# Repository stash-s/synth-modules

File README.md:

# synth-modules

Analog Synth Modules schematics shamelessly copied from Internets.

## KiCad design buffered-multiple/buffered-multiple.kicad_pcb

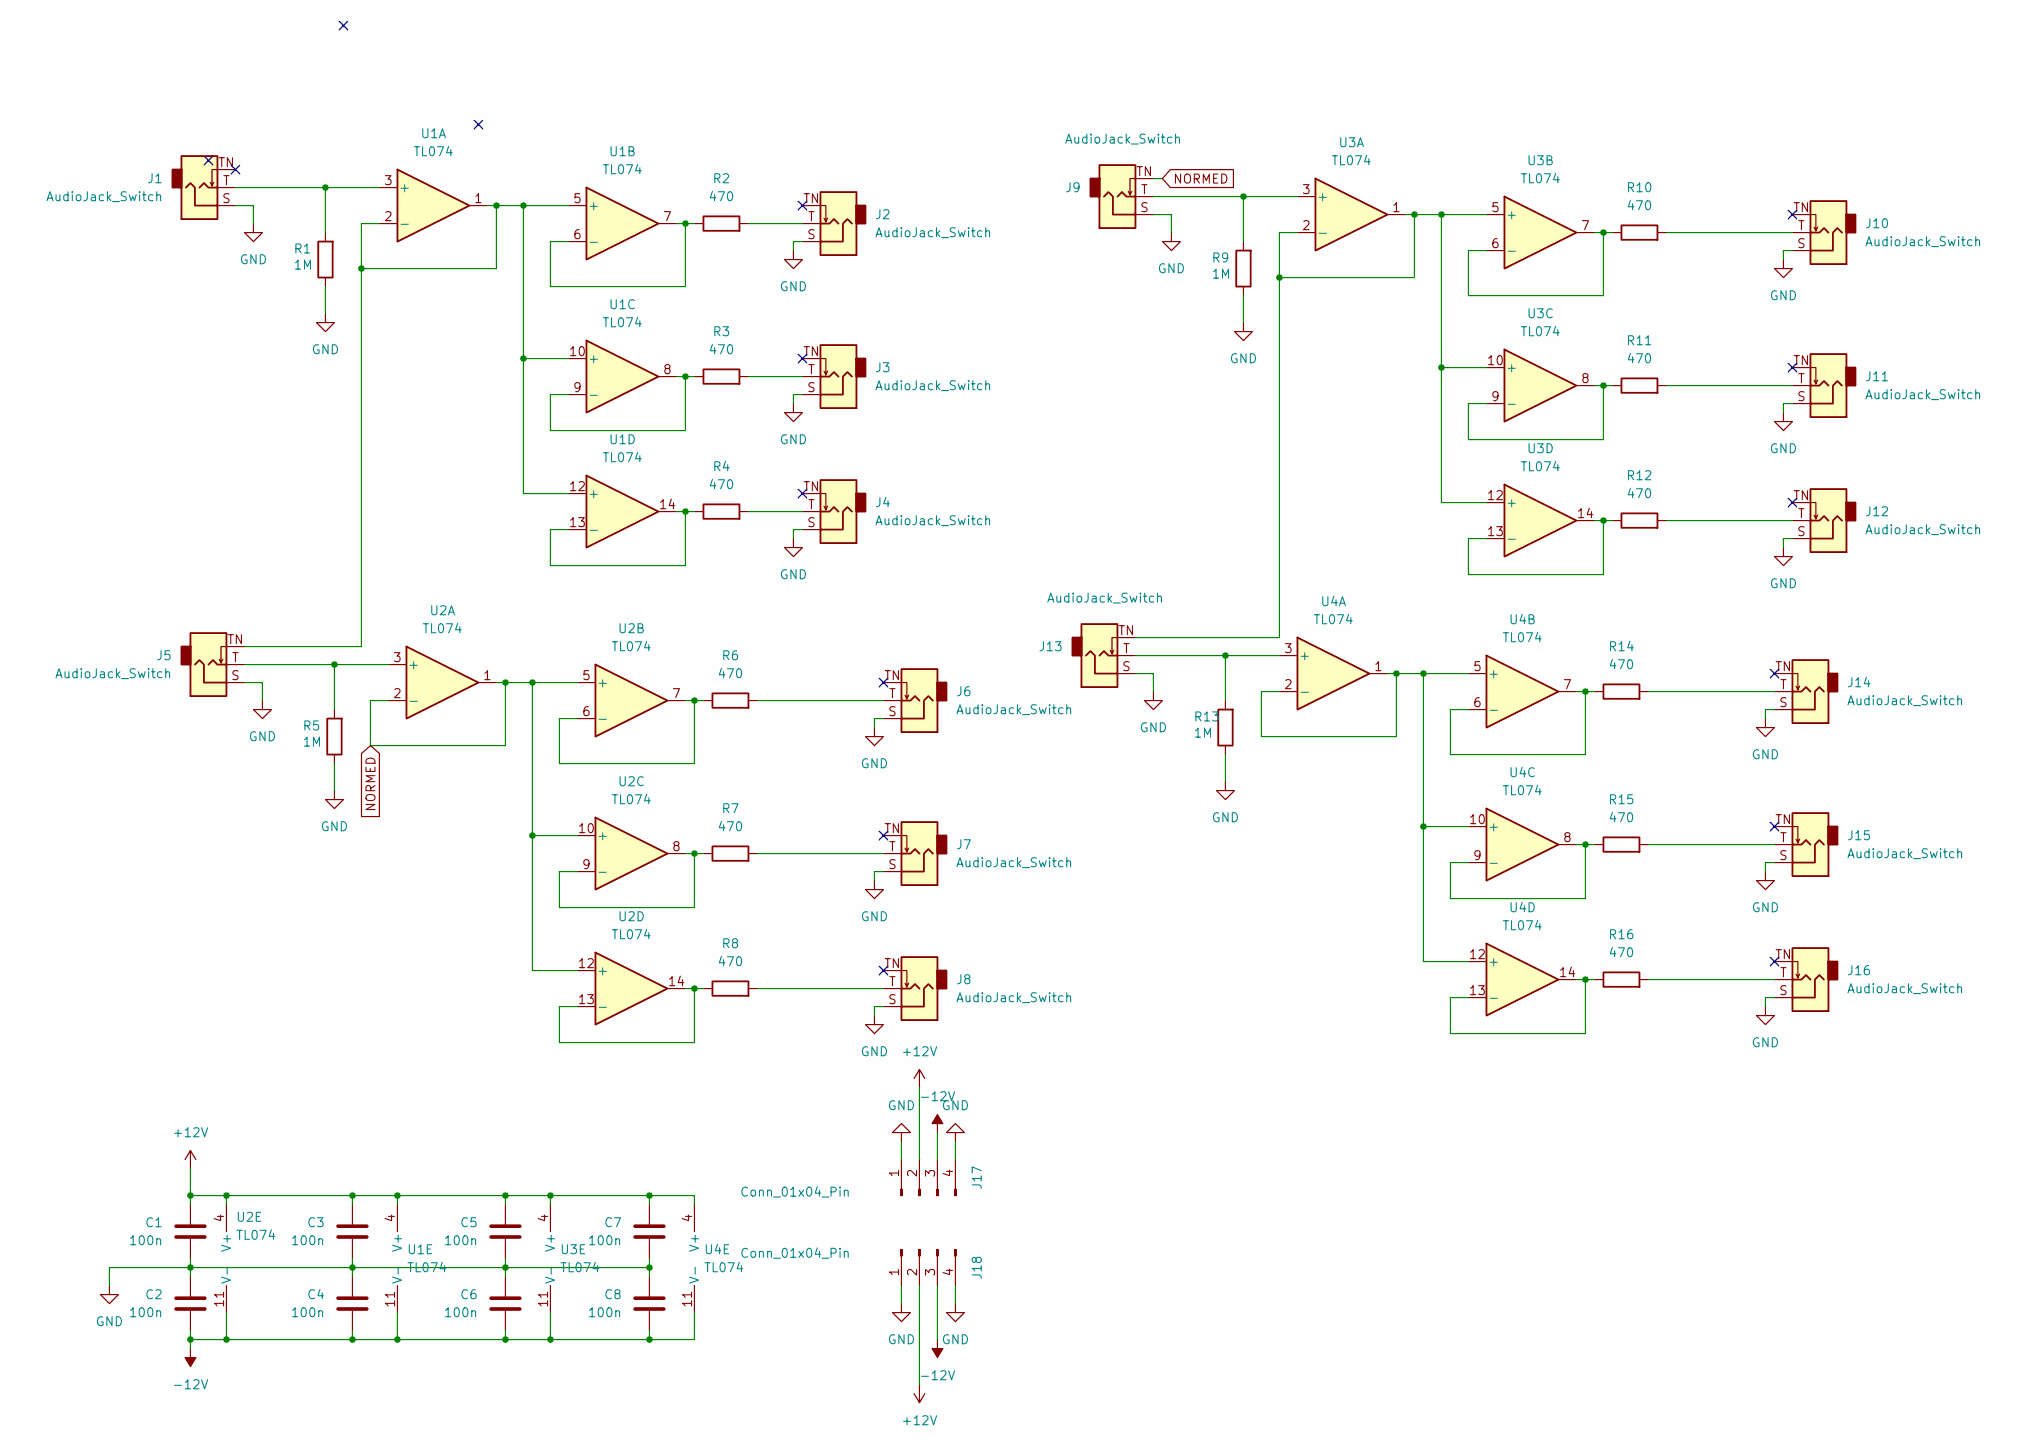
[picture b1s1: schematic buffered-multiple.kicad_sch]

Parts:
C1, C2, C3, C4, C5, C6, C7, C8: 100n; C_0402_1005Metric
J1, J2, J3, J4, J5, J6, J7, J8, J9, J10, J11, J12, J13, J14, J15, J16: AudioJack_Switch; Jack_3.5mm_Switch
J17, J18: Conn_01x04_Pin; PinHeader_1x04_P2.54mm_Vertical
R1, R5, R9, R13: 1M; R_0402_1005Metric
R2, R3, R4, R6, R7, R8, R10, R11, R12, R14, R15, R16: 470; R_0402_1005Metric
U1, U2, U3, U4: TL074; SOT-23-THIN-14_2x4.2mm_P0.5mm

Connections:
+12V: C1.1, C3.1, C5.1, C7.1, J17.2, J18.2, U1.4 (V+), U2.4 (V+), U3.4 (V+), U4.4 (V+)
-12V: C2.2, C4.2, C6.2, C8.2, J17.3, J18.3, U1.11 (V-), U2.11 (V-), U3.11 (V-), U4.11 (V-)
GND: C1.2, C2.1, C3.2, C4.1, C5.2, C6.1, C7.2, C8.1, J1.S, J2.S, J3.S, J4.S, J5.S, J6.S, J7.S, J8.S, J9.S, J10.S, J11.S, J12.S, J13.S, J14.S, J15.S, J16.S, J17.1, J17.4, J18.1, J18.4, R1.1, R5.1, R9.1, R13.1
NORMED: J9.TN, U2.1, U2.2 (-), U2.5 (+), U2.10 (+), U2.12 (+)
unnamed: J2.T, R2.2
unnamed: J3.T, R3.2
unnamed: J4.T, R4.2
unnamed: J6.T, R6.2
unnamed: J7.T, R7.2
unnamed: J8.T, R8.2
unnamed: J10.T, R10.2
unnamed: J11.T, R11.2
unnamed: J12.T, R12.2
unnamed: J14.T, R14.2
unnamed: J15.T, R15.2
unnamed: J16.T, R16.2
unnamed: J1.T, R1.2, U1.3 (+)
unnamed: J5.TN, U1.1, U1.2 (-), U1.5 (+), U1.10 (+), U1.12 (+)
unnamed: R2.1, U1.6 (-), U1.7
unnamed: R3.1, U1.8, U1.9 (-)
unnamed: R4.1, U1.13 (-), U1.14
unnamed: J5.T, R5.2, U2.3 (+)
unnamed: R6.1, U2.6 (-), U2.7
unnamed: R7.1, U2.8, U2.9 (-)
unnamed: R8.1, U2.13 (-), U2.14
unnamed: J9.T, R9.2, U3.3 (+)
unnamed: J13.TN, U3.1, U3.2 (-), U3.5 (+), U3.10 (+), U3.12 (+)
unnamed: R10.1, U3.6 (-), U3.7
unnamed: R11.1, U3.8, U3.9 (-)
unnamed: R12.1, U3.13 (-), U3.14
unnamed: J13.T, R13.2, U4.3 (+)
unnamed: U4.1, U4.2 (-), U4.5 (+), U4.10 (+), U4.12 (+)
unnamed: R14.1, U4.6 (-), U4.7
unnamed: R15.1, U4.8, U4.9 (-)
unnamed: R16.1, U4.13 (-), U4.14

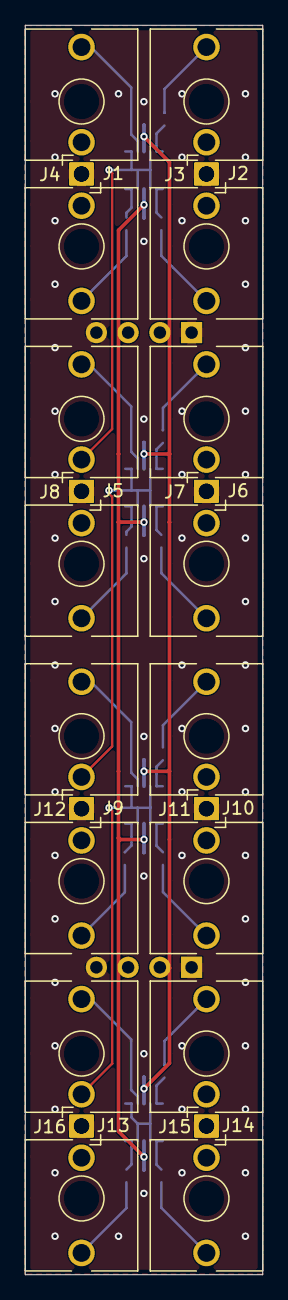
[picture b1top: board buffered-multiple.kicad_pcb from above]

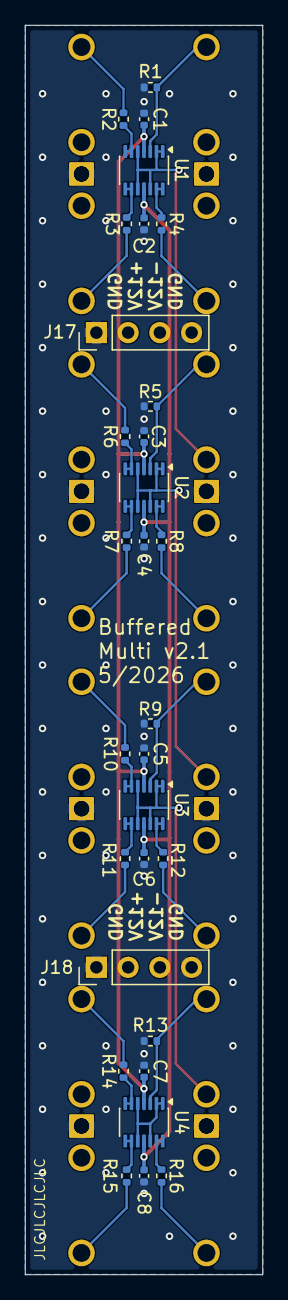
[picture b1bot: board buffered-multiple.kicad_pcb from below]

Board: 2 copper layers, 19.0 x 100.0 mm, 46 parts (30 on the bottom side), 35 nets.

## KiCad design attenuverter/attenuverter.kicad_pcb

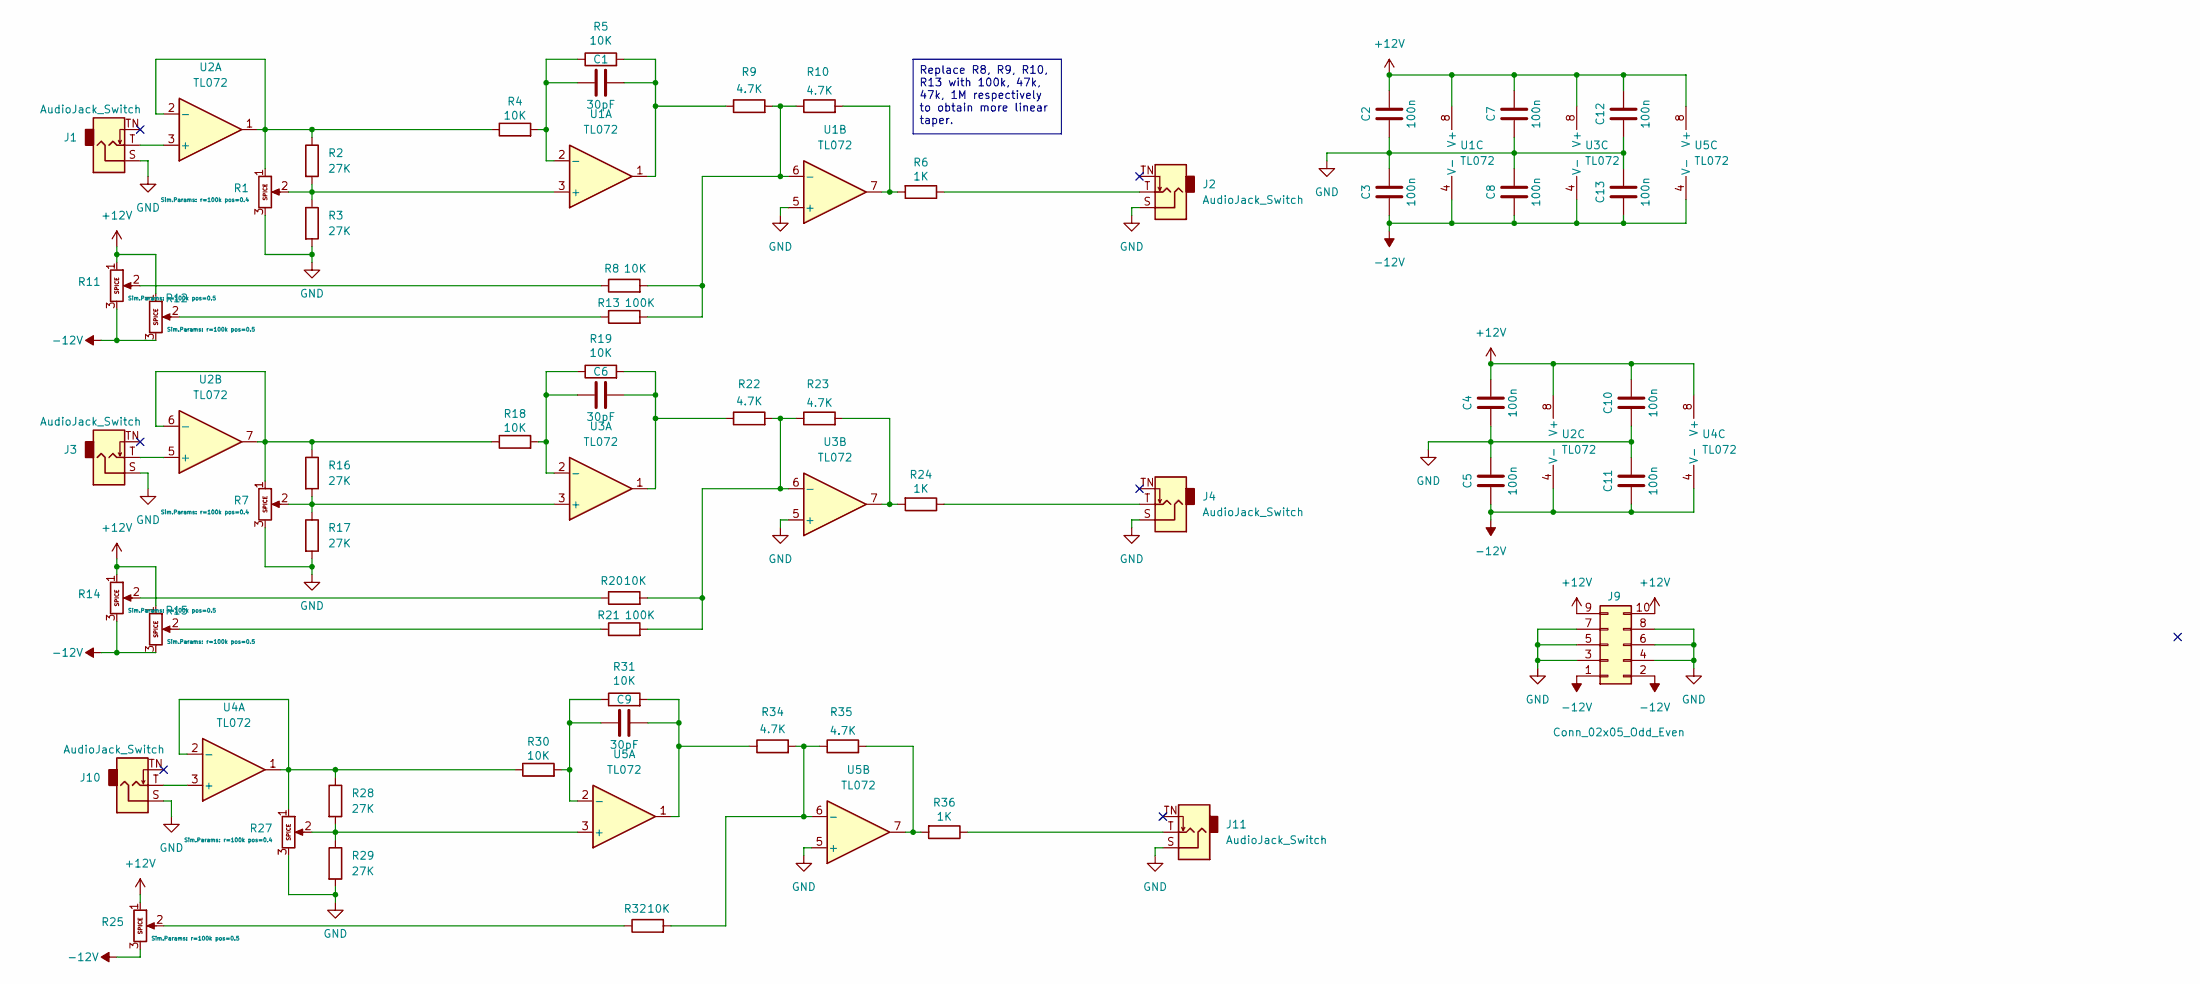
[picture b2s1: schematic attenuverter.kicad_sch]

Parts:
C1, C6, C9: 30pF; C_0402_1005Metric
C2, C3, C4, C5, C7, C8, C10, C11, C12, C13: 100n; C_0402_1005Metric
J1, J2, J3, J4, J10, J11: AudioJack_Switch; Jack_3.5mm_Switch
J9: Conn_02x05_Odd_Even; IDC-Header_2x05_P2.54mm_Vertical
R1, R7, R11, R12, R14, R15, R25, R27: 100K; Potentiometer_Alpha_RD901F-40-00D_Single_Vertical
R2, R3, R16, R17, R28, R29: 27K; R_0402_1005Metric
R4, R5, R18, R19, R30, R31: 10K; R_0402_1005Metric
R6, R24, R36: 1K; R_0402_1005Metric
R8, R20, R32: 10K; R_Axial_DIN0204_L3.6mm_D1.6mm_P5.08mm_Horizontal
R9, R10, R22, R23, R34, R35: 4.7K; R_Axial_DIN0204_L3.6mm_D1.6mm_P5.08mm_Horizontal
R13, R21: 100K; R_Axial_DIN0204_L3.6mm_D1.6mm_P5.08mm_Horizontal
U1, U2, U3, U4, U5: TL072; SOT-23-8

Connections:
+12V: C2.2, C4.2, C7.2, C10.2, C12.2, J9.9, J9.10, R11.1, R12.1, R14.1, R15.1, R25.1, U1.8 (V+), U2.8 (V+), U3.8 (V+), U4.8 (V+), U5.8 (V+)
-12V: C3.1, C5.1, C8.1, C11.1, C13.1, J9.1, J9.2, R11.3, R12.3, R14.3, R15.3, R25.3, U1.4 (V-), U2.4 (V-), U3.4 (V-), U4.4 (V-), U5.4 (V-)
GND: C2.1, C3.2, C4.1, C5.2, C7.1, C8.2, C10.1, C11.2, C12.1, C13.2, J1.S, J2.S, J3.S, J4.S, J9.3, J9.4, J9.5, J9.6, J9.7, J9.8, J10.S, J11.S, R1.3, R3.2, R7.3, R17.2, R27.3, R29.2, U1.5 (+), U3.5 (+), U5.5 (+)
unnamed: C1.1, R5.2, R9.1, U1.1
unnamed: C6.2, R19.2, R22.1, U3.1
unnamed: C9.2, R31.2, R34.1, U5.1
unnamed: J2.T, R6.1
unnamed: J4.T, R24.1
unnamed: J11.T, R36.1
unnamed: R6.2, R10.2, U1.7
unnamed: R8.1, R11.2
unnamed: R12.2, R13.1
unnamed: R14.2, R20.1
unnamed: R15.2, R21.1
unnamed: R23.2, R24.2, U3.7
unnamed: R25.2, R32.1
unnamed: R35.2, R36.2, U5.7
unnamed: R1.2, R2.2, R3.1, U1.3 (+)
unnamed: C1.2, R4.2, R5.1, U1.2 (-)
unnamed: R8.2, R9.2, R10.1, R13.2, U1.6 (-)
unnamed: J1.T, U2.3 (+)
unnamed: R1.1, R2.1, R4.1, U2.1, U2.2 (-)
unnamed: J3.T, U2.5 (+)
unnamed: R7.1, R16.1, R18.1, U2.6 (-), U2.7
unnamed: R7.2, R16.2, R17.1, U3.3 (+)
unnamed: C6.1, R18.2, R19.1, U3.2 (-)
unnamed: R20.2, R21.2, R22.2, R23.1, U3.6 (-)
unnamed: J10.T, U4.3 (+)
unnamed: R27.1, R28.1, R30.1, U4.1, U4.2 (-)
unnamed: R27.2, R28.2, R29.1, U5.3 (+)
unnamed: C9.1, R30.2, R31.1, U5.2 (-)
unnamed: R32.2, R34.2, R35.1, U5.6 (-)

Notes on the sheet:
Replace R8, R9, R10, R13 with 100k, 47k, 47k, 1M respectively to obtain more linear taper.

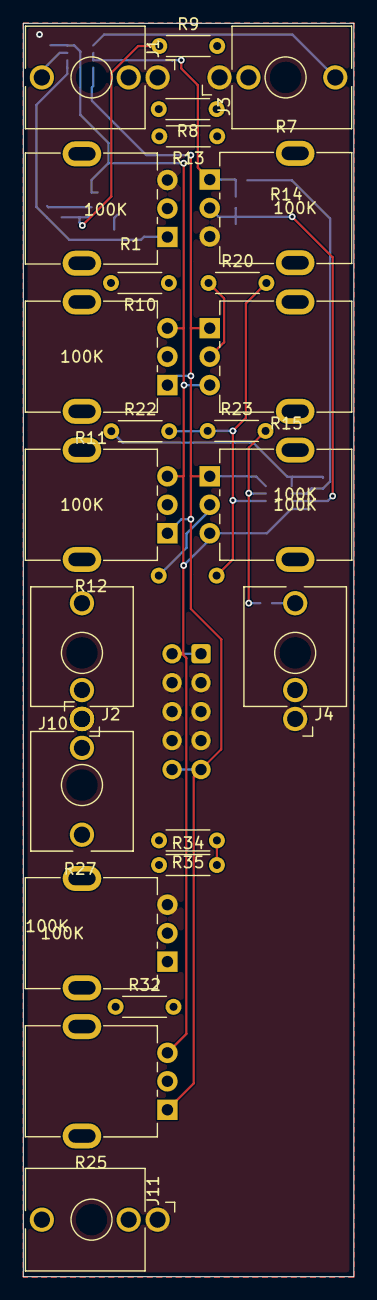
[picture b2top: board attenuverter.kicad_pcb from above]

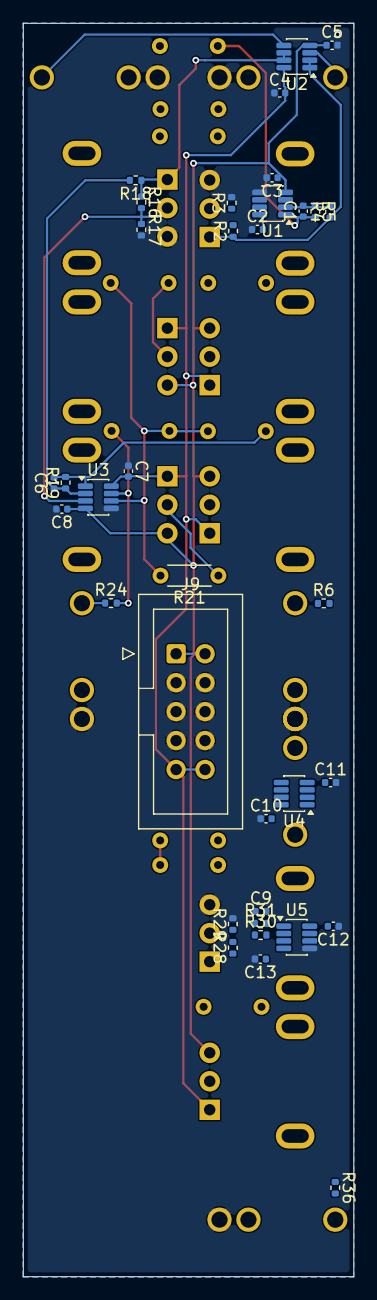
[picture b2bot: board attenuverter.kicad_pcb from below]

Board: 2 copper layers, 29.0 x 110.0 mm, 59 parts (35 on the bottom side), 32 nets.

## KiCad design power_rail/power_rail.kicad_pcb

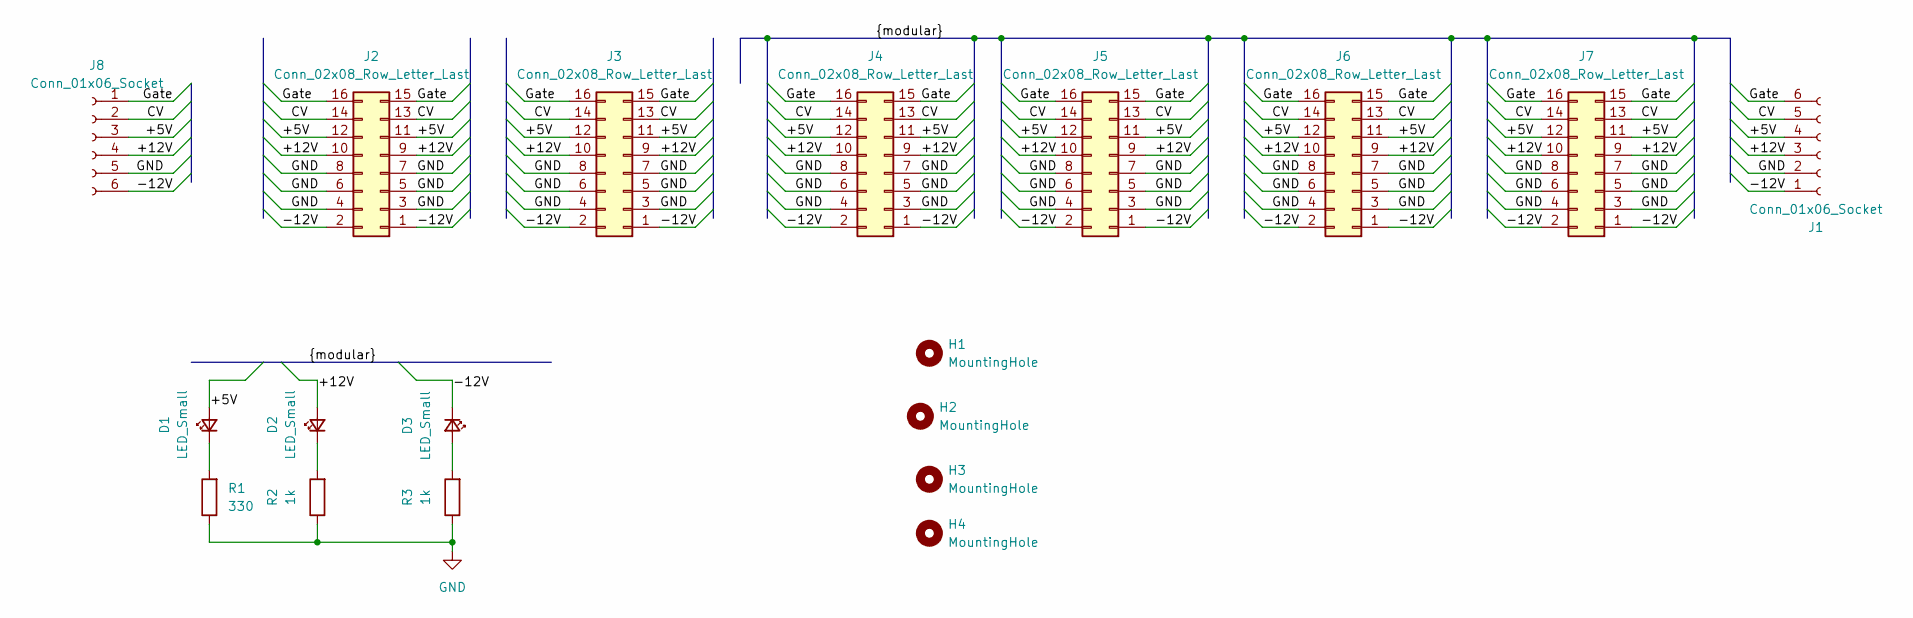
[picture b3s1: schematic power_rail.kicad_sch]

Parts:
D1, D2, D3: LED_Small; LED_D3.0mm
H1, H2, H3, H4: MountingHole; MountingHole_3.2mm_M3
J1, J8: Conn_01x06_Socket; TerminalBlock_Phoenix_MKDS-1,5-6-5.08_1x06_P5.08mm_Horizont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
J2, J3, J4, J5, J6, J7: Conn_02x08_Row_Letter_Last; IDC-Header_2x08_P2.54mm_Vertical
R1: 330; R_Axial_DIN0207_L6.3mm_D2.5mm_P7.62mm_Horizontal
R2, R3: 1k; R_Axial_DIN0207_L6.3mm_D2.5mm_P7.62mm_Horizontal

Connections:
/+5V: D1.2 (A), J1.4, J2.11, J2.12, J3.11, J3.12, J4.11, J4.12, J5.11, J5.12, J6.11, J6.12, J7.11, J7.12, J8.3
/+12V: D2.2 (A), J1.3, J2.9, J2.10, J3.9, J3.10, J4.9, J4.10, J5.9, J5.10, J6.9, J6.10, J7.9, J7.10, J8.4
/-12V: D3.1 (K), J1.1, J2.1, J2.2, J3.1, J3.2, J4.1, J4.2, J5.1, J5.2, J6.1, J6.2, J7.1, J7.2, J8.6
/CV: J1.5, J2.13, J2.14, J3.13, J3.14, J4.13, J4.14, J5.13, J5.14, J6.13, J6.14, J7.13, J7.14, J8.2
/Gate: J1.6, J2.15, J2.16, J3.15, J3.16, J4.15, J4.16, J5.15, J5.16, J6.15, J6.16, J7.15, J7.16, J8.1
GND: J1.2, J2.3, J2.4, J2.5, J2.6, J2.7, J2.8, J3.3, J3.4, J3.5, J3.6, J3.7, J3.8, J4.3, J4.4, J4.5, J4.6, J4.7, J4.8, J5.3, J5.4, J5.5, J5.6, J5.7, J5.8, J6.3, J6.4, J6.5, J6.6, J6.7, J6.8, J7.3, J7.4, J7.5, J7.6, J7.7, J7.8, J8.5, R1.1, R2.1, R3.1
unnamed: D1.1 (K), R1.2
unnamed: D2.1 (K), R2.2
unnamed: D3.2 (A), R3.2

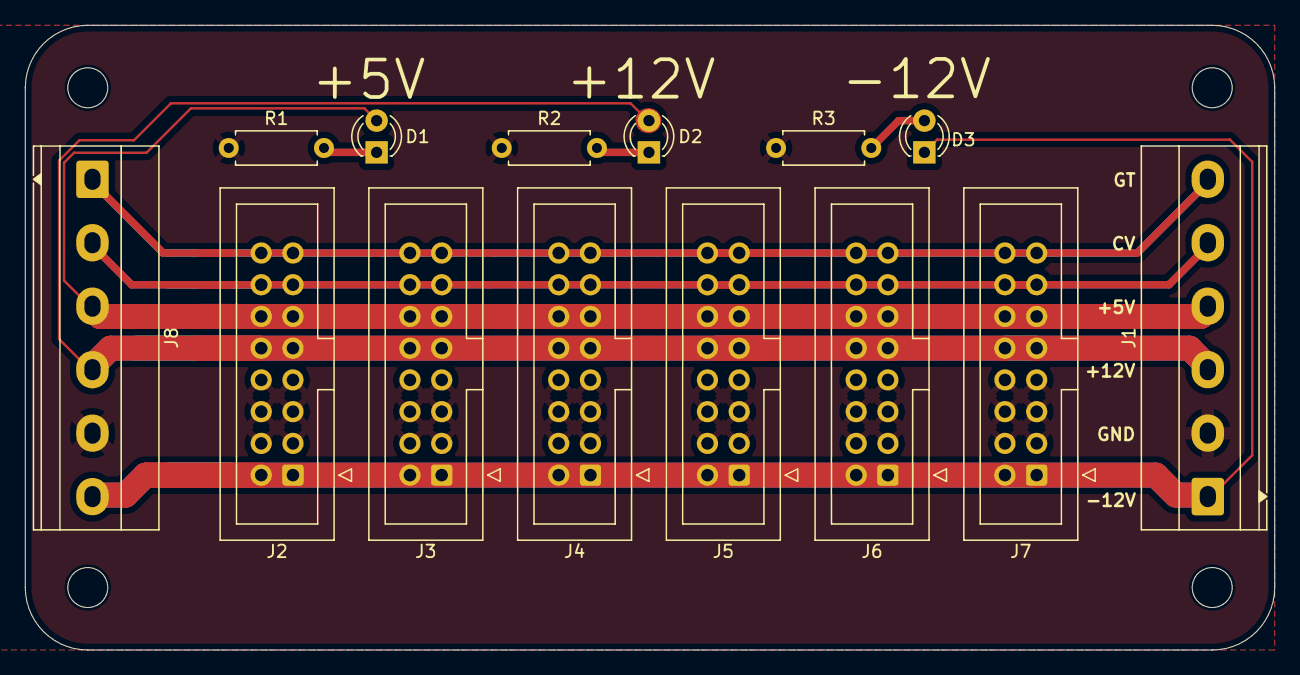
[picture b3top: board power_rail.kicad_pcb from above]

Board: 2 copper layers, 100.0 x 50.0 mm, 18 parts (0 on the bottom side), 9 nets.

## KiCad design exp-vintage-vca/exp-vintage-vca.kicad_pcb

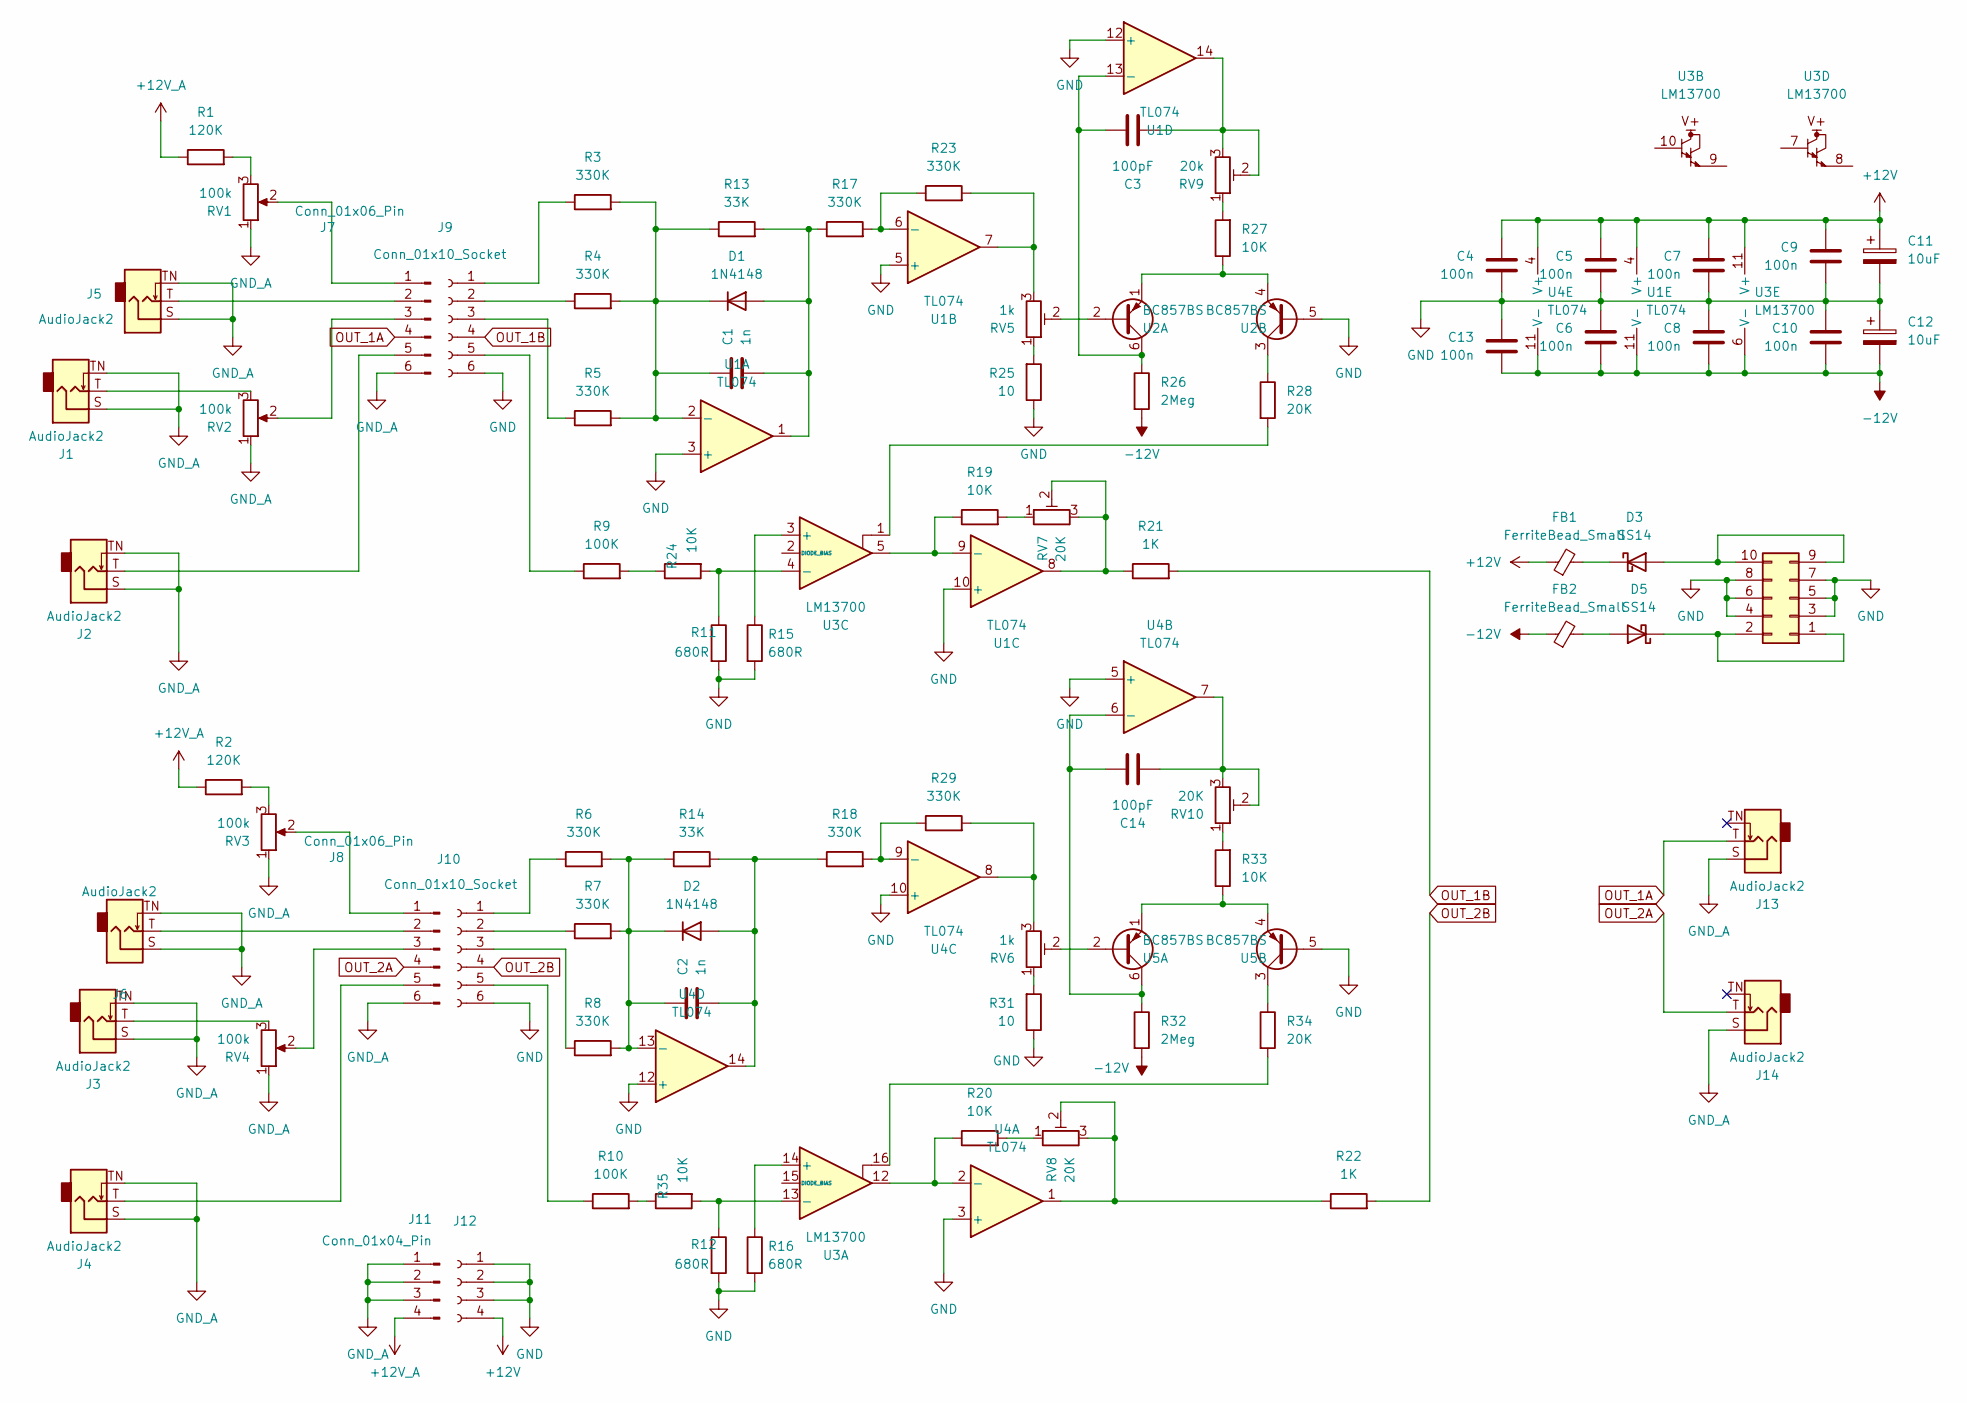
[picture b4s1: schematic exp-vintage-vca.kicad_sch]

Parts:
C1, C2: 1n; C_0805_2012Metric_Pad1.18x1.45mm_HandSolder; LCSC C46653
C3, C14: 100pF; C_0805_2012Metric_Pad1.18x1.45mm_HandSolder; LCSC C1790
C4, C5, C6, C7, C8, C9, C10, C13: 100n; C_0805_2012Metric_Pad1.18x1.45mm_HandSolder; LCSC C49678
C11, C12: 10uF; CP_Radial_D5.0mm_P2.50mm; LCSC C13585
D1, D2: 1N4148; D_SOD-123; LCSC C81598
D3, D5: SS14; D_SMA
FB1, FB2: FerriteBead_Small; Ferrite_Bead_5mm_3.5mm_Horizontal
J1, J2, J3, J4, J5, J6, J13, J14: AudioJack2; Jack_3.5mm_Switch
J7, J8: Conn_01x06_Pin; PinHeader_1x06_P2.54mm_Vertical
J9, J10: Conn_01x10_Socket; PinSocket_1x06_P2.54mm_Vertical
J11: Conn_01x04_Pin; PinHeader_1x04_P2.54mm_Vertical
J12: Conn_01x04_Socket; PinSocket_1x04_P2.54mm_Vertical
J15: Conn_02x08_Odd_Even; IDC-Header_2x05_P2.54mm_Vertical
R1, R2: 120K; R_Axial_DIN0207_L6.3mm_D2.5mm_P7.62mm_Horizontal
R3, R4, R5, R6, R7, R8, R17, R18, R23, R29: 330K; R_0603_1608Metric_Pad0.98x0.95mm_HandSolder; LCSC C23137
R9, R10: 100K; R_0603_1608Metric_Pad0.98x0.95mm_HandSolder; LCSC C25803
R11, R12, R15, R16: 680R; R_0603_1608Metric_Pad0.98x0.95mm_HandSolder; LCSC C23228
R13, R14: 33K; R_0603_1608Metric_Pad0.98x0.95mm_HandSolder; LCSC C4216
R19, R20: 10K; R_0603_1608Metric_Pad0.98x0.95mm_HandSolder; LCSC C4184
R21, R22: 1K; R_0603_1608Metric_Pad0.98x0.95mm_HandSolder; LCSC C21190
R24, R35: 10K; R_0603_1608Metric_Pad0.98x0.95mm_HandSolder; LCSC C25804
R25, R31: 10; R_0603_1608Metric_Pad0.98x0.95mm_HandSolder; LCSC C23138
R26, R32: 2Meg; R_0603_1608Metric_Pad0.98x0.95mm_HandSolder; LCSC C22935
R27, R33: 10K; R_0603_1608Metric_Pad0.98x0.95mm_HandSolder; LCSC C31850
R28, R34: 20K; R_0603_1608Metric_Pad0.98x0.95mm_HandSolder; LCSC C23212
RV1, RV2, RV3, RV4: 100k; Potentiometer_Alpha_RD901F-40-00D_Single_Vertical
RV5, RV6: 1k; Potentiometer_Bourns_3296W_Vertical
RV7, RV8, RV10: 20K; Potentiometer_Bourns_3296W_Vertical
RV9: 20k; Potentiometer_Bourns_3296W_Vertical
U1, U4: TL074; SOT-23-THIN-14_2x4.2mm_P0.5mm; LCSC C5116353
U2, U5: BC857BS; SOT-363_SC-70-6; LCSC C8654
U3: LM13700; SOIC-16_3.9x9.9mm_P1.27mm; LCSC C174050

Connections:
+12V: C4.1, C5.1, C7.1, C9.1, C11.1, FB1.1, J12.4, U1.4 (V+), U3.11 (V+), U4.4 (V+)
+12V_A: J11.4, R1.1, R2.1
-12V: C6.2, C8.2, C10.2, C12.2, C13.2, FB2.1, R26.2, R32.2, U1.11 (V-), U3.6 (V-), U4.11 (V-)
GND: C4.2, C5.2, C6.1, C7.2, C8.1, C9.2, C10.1, C11.2, C12.1, C13.1, J9.6, J10.6, J12.1, J12.2, J12.3, J15.3, J15.4, J15.5, J15.6, J15.7, J15.8, R11.2, R12.2, R15.2, R16.2, R25.1, R31.1, U1.3 (+), U1.5 (+), U1.10 (+), U1.12 (+), U2.5 (B2), U4.3 (+), U4.5 (+), U4.10 (+), U4.12 (+), U5.5 (B2)
GND_A: J1.S, J1.TN, J2.S, J2.TN, J3.S, J3.TN, J4.S, J4.TN, J5.S, J5.TN, J6.S, J6.TN, J7.6, J8.6, J11.1, J11.2, J11.3, J13.S, J14.S, RV1.1, RV2.1, RV3.1, RV4.1
unnamed: C3.2, RV9.2, RV9.3, U1.14
unnamed: C14.2, RV10.2, RV10.3, U4.7
unnamed: C1.2, D1.2 (A), R13.2, R17.1, U1.1
unnamed: C1.1, D1.1 (K), R3.2, R4.2, R5.2, R13.1, U1.2 (-)
unnamed: C2.2, D2.2 (A), R14.2, R18.1, U4.14
unnamed: C2.1, D2.1 (K), R6.2, R7.2, R8.2, R14.1, U4.13 (-)
unnamed: D3.2 (A), J15.9, J15.10
unnamed: D3.1 (K), FB1.2
unnamed: D5.2 (A), FB2.2
unnamed: D5.1 (K), J15.1, J15.2
unnamed: J1.T, RV2.3
unnamed: J3.T, RV4.3
unnamed: J7.1, RV1.2
unnamed: J5.T, J7.2
unnamed: J7.3, RV2.2
unnamed: J2.T, J7.5
unnamed: J8.1, RV3.2
unnamed: J6.T, J8.2
unnamed: J8.3, RV4.2
unnamed: J4.T, J8.5
unnamed: J9.1, R3.1
unnamed: J9.2, R4.1
unnamed: J9.3, R5.1
unnamed: J9.5, R9.1
unnamed: J10.1, R6.1
unnamed: J10.2, R7.1
unnamed: J10.3, R8.1
unnamed: J10.5, R10.1
unnamed: R1.2, RV1.3
unnamed: R2.2, RV3.3
unnamed: R10.2, R35.1
unnamed: R19.2, RV7.1
unnamed: R20.2, RV8.1
unnamed: R21.1, RV7.2, RV7.3, U1.8
unnamed: R22.1, RV8.2, RV8.3, U4.1
unnamed: R23.2, RV5.3, U1.7
unnamed: R9.2, R24.1
unnamed: R25.2, RV5.1
unnamed: R27.2, RV9.1
unnamed: R28.2, U3.1
unnamed: R29.2, RV6.3, U4.8
unnamed: R31.2, RV6.1
unnamed: R33.2, RV10.1
unnamed: R34.2, U3.16
unnamed: R17.2, R23.1, U1.6 (-)
unnamed: R19.1, U1.9 (-), U3.5
unnamed: C3.1, R26.1, U1.13 (-), U2.6 (C1)
unnamed: RV5.2, U2.2 (B1)
unnamed: R27.1, U2.1 (E1), U2.4 (E2)
unnamed: R28.1, U2.3 (C2)
unnamed: R16.1, U3.14 (+)
unnamed: R12.1, R35.2, U3.13 (-)
unnamed: R15.1, U3.3 (+)
unnamed: R11.1, R24.2, U3.4 (-)
unnamed: R20.1, U3.12, U4.2 (-)
unnamed: C14.1, R32.1, U4.6 (-), U5.6 (C1)
unnamed: R18.2, R29.1, U4.9 (-)
unnamed: RV6.2, U5.2 (B1)
unnamed: R33.1, U5.1 (E1), U5.4 (E2)
unnamed: R34.1, U5.3 (C2)
OUT_1A: J7.4, J13.T
OUT_1B: J9.4, R21.2
OUT_2A: J8.4, J14.T
OUT_2B: J10.4, R22.2

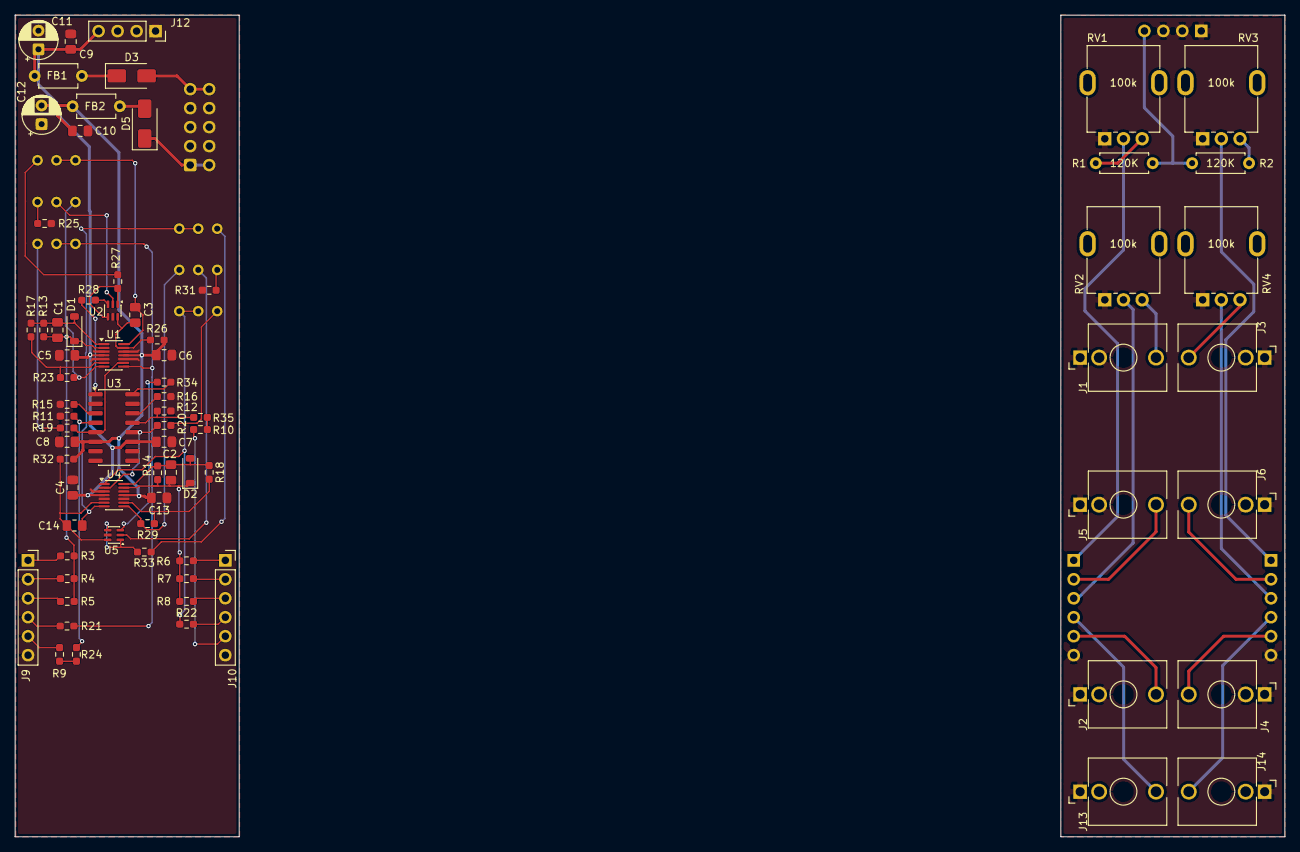
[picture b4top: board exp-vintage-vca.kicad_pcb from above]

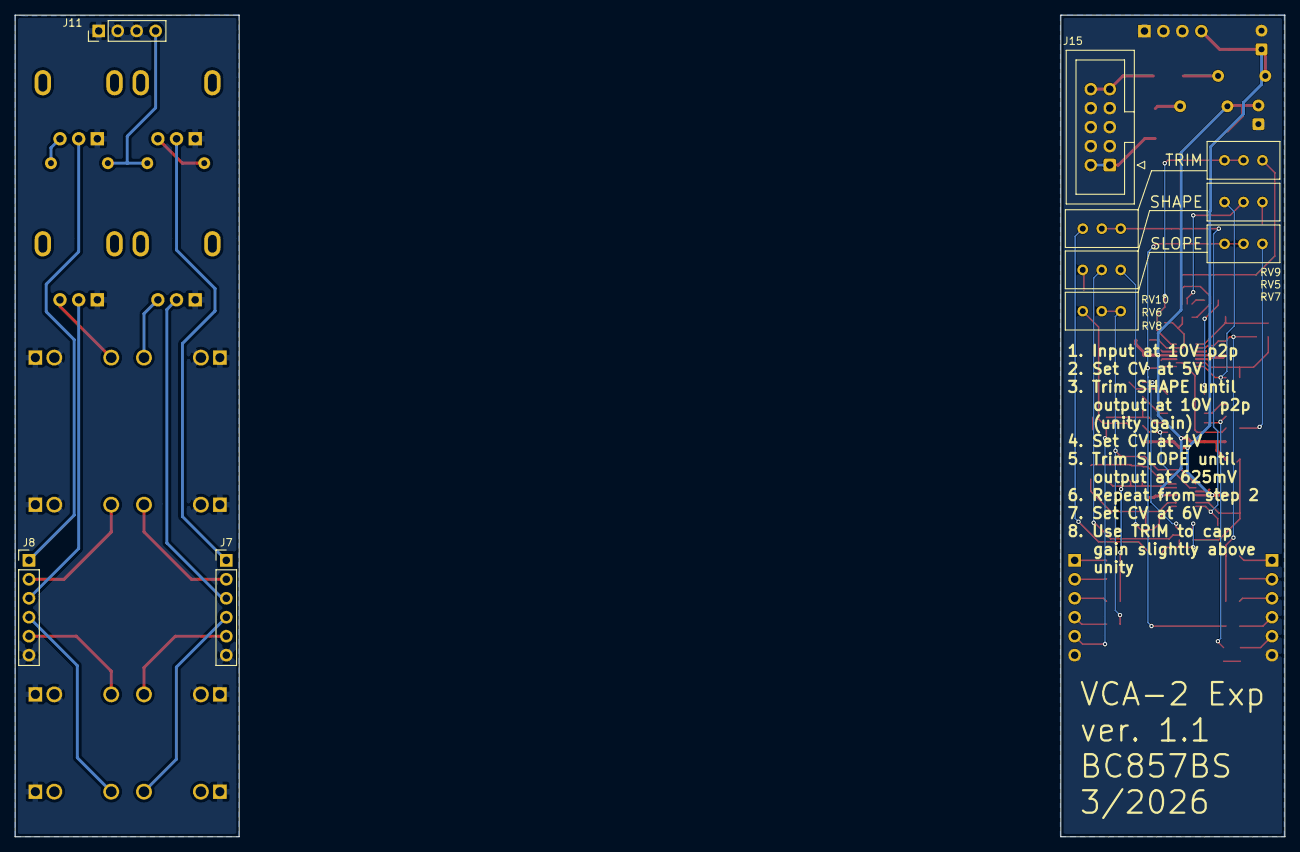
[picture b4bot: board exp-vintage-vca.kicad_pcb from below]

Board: 2 copper layers, 170.0 x 110.0 mm, 86 parts (10 on the bottom side), 69 nets.

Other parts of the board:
A: Board
B: Board
